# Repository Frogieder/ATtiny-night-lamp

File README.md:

# ATtiny night lamp

## This project is still in development!
Even though this project is mostly functional at this point, yet some changes are still going to be made. The code is what's going to change the most, but the schematic might get changed too if it's necessary. 

## About the project

This repo contains all the files needed to make a night lamp powered by ATtiny.
Compatible MCUs are:
* ATtiny13
* ATtiny25
* ATtiny45
* ATtiny85
* possibly some other MCUs with minor and/or major tweaks

### Features:

* 4 LEDs to light up your room so you can find a way to your bed
* a switch to fully disable the lamp
* capacitive touch sensor to manually control the lamp
* low power operation, MCU sleeps when the LEDs are off
* photoresistor to automatically turn the lamp on when it's dark
* PWM controller to slowly fade out the LEDs

# Make your own

**Beware, this project is still in active development and anything, including the circuit and the code may change**

## PCB
The folder 'schematics-boards' contains Eagle files, so you can export files in any format you need. You will need MMBF170 library downloaded in '~/EAGLE/libraries/MMBF170.lbr'. There is also a pdf (outdated) which contains exported file you can use if you are going to make the PCB using the photosensitive method. For toner transfer, you will need to mirror the design to be able to make it.

## Construction
### List of components:
* 1x MCU (Attiny85 or some other, discussed above)
* 1x THT photoresistor
* Resistors, 1206 package: 
    * 2x 15k - pulldowns, higher values than usual were chosen to minimize power usage
    * 1x 8M2 - sets the touch sensor sensitivity, higher values -> higher sensitivity
    * 1x 1M - creates volatge divider together with the photoresistor, choose your value based on your photoresistor
    4x 470R - LED current limiting resistor, y'know, not to burn them
* 1x 100nF capacitor
* 4x white LED, ideally with diffuser, or you can add an external one
* 1x THT switch
* 1x MMBF170 MOSFET
* PCB
* some cables
* conductive plate that can be used for the capacitive touch switch
* 4.5V batery

Assembly instructions: 
* Upload the program to the ATtiny
* Solder everything according to .brd file.
* Make the touch switch and attach it to its hole with a cable. 
* Solder the batery wires into the board and attach both the PCB and the touch switch to the batery holder.

To make the instructions clearer, I'll add some photos of my build once it's fully completed.

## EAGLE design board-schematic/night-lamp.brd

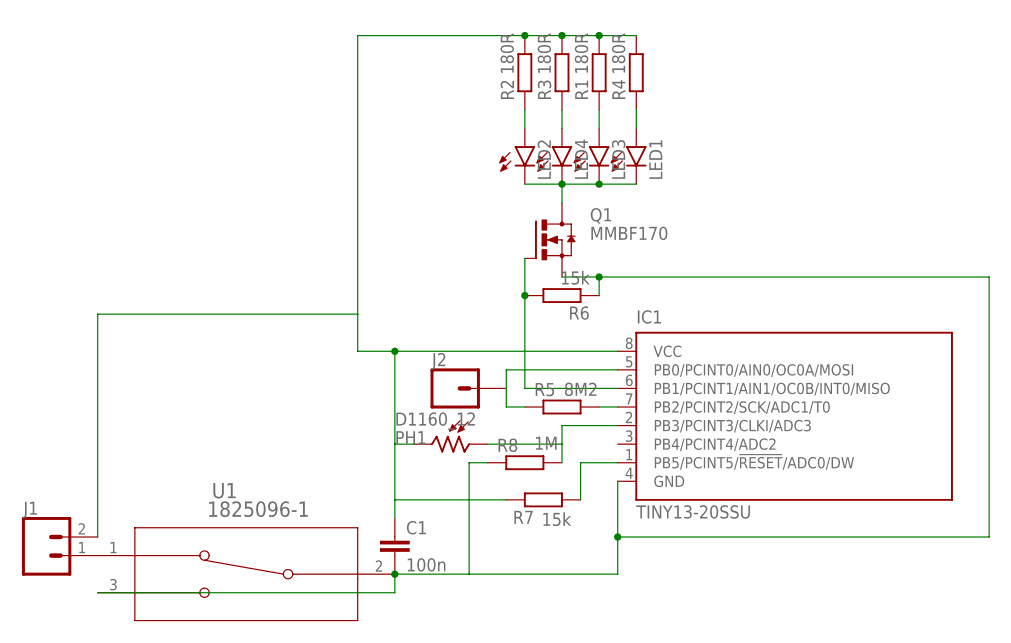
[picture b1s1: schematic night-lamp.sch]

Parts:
C1: 100n; C1206
IC1: TINY13-20SSU; 8S1
J1: CONN_02; 1X02
J2: CONN_01; 1X01
LED1, LED2, LED3, LED4: LED5MM
PH1: D1160_12; D11XX
Q1: MMBF170; SOT23
R1, R2, R3, R4: 180R; R1206
R5: 8M2; R1206
R6, R7: 15k; R1206
R8: 1M; R1206
U1: 1825096-1; SW3-TOGGLE-2POL_P100

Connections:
unnamed: C1.1, IC1.8 (VCC), J1.2, PH1.2, R1.2, R2.2, R3.2, R4.2, R7.2
unnamed: C1.2, IC1.4 (GND), Q1.2 (S), R6.1, R8.1, U1.2 (3), U1.3 (2)
unnamed: LED2.A, R2.1
unnamed: LED4.A, R3.1
unnamed: LED3.A, R1.1
unnamed: LED1.A, R4.1
unnamed: LED1.K (C), LED2.K (C), LED3.K (C), LED4.K (C), Q1.3 (D)
unnamed: IC1.7 (PB2/PCINT2/SCK/ADC1/T0), R5.2
unnamed: IC1.6 (PB1/PCINT1/AIN1/OC0B/INT0/MISO), Q1.1 (G), R6.2
unnamed: IC1.5 (PB0/PCINT0/AIN0/OC0A/MOSI), J2.1, R5.1
unnamed: J1.1, U1.1
unnamed: IC1.2 (PB3/PCINT3/CLKI/ADC3), PH1.1, R8.2
unnamed: IC1.1 (PB5/PCINT5/!RESET!/ADC0/DW), R7.1

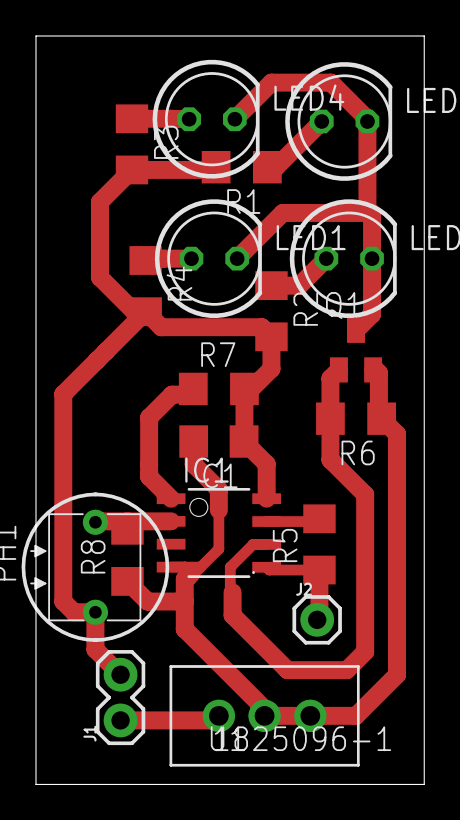
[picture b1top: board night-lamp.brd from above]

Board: 2 copper layers, 21.6 x 41.6 mm, 19 parts (0 on the bottom side), 13 nets.

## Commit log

2021-09-12 Toggle LEDs with a touch
2021-09-19 Add PWM support
    Set most of PWM registers in pwm_init, except for Compare Match Output
    Mode. Setting it while OCR is 0 results in weird flashing. COM01 has to
    be cleared every time OCR is set to 0.
2021-09-19 Update schematics
    Add a resistor between GND and ADC3 (pin 2) on ATtiny. This change is
    needed to create a voltage divider between +5V and GND, where the ADC
    measures its output.
2021-11-05 Theoretically working light sensor
    Implement adc functionality and control logic to automatically
    turn on the lamp when it's dark. Since I don't have the hardware
    with me, I cannot test it now, so it's likely not to work.
2021-11-05 Update README and TO DO
    Add some more instructions to the README and make everything clearer.
    Finally.

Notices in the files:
parts and their libraries:
SparkFun-Connectors: Licensing: Creative Commons ShareAlike 4.0 International - https://creativecommons.org/licenses/by-sa/4.0
COPYRIGHT: Copyright (C) 2016 Accelerated Designs. All rights reserved
